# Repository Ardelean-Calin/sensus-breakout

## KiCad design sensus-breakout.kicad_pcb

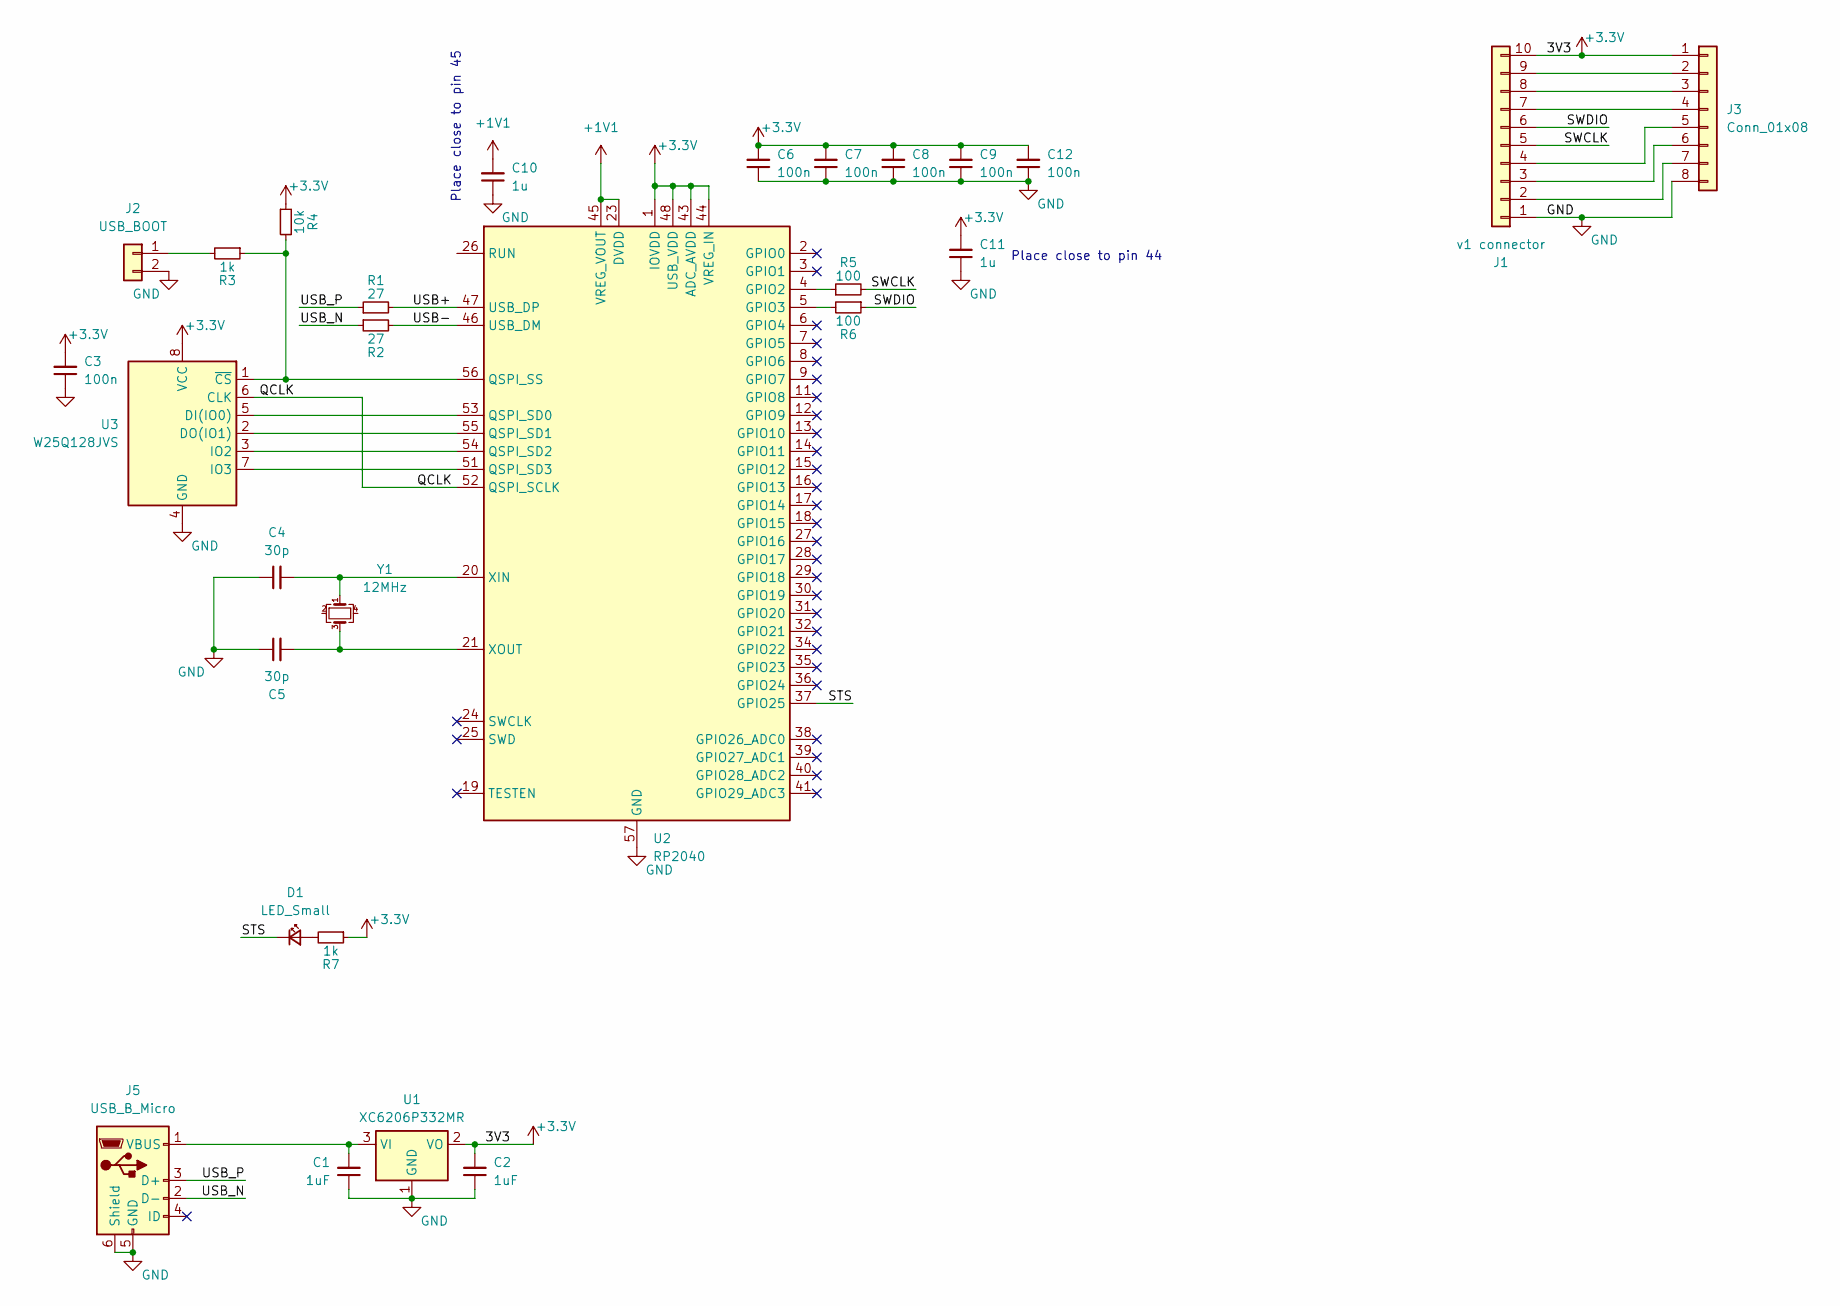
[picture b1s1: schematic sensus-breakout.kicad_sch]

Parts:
C1, C2: 1uF; C_0402_1005Metric; LCSC C52923
C3, C6, C7, C8, C9, C12: 100n; C_0402_1005Metric; LCSC C307331
C4, C5: 30p; C_0402_1005Metric; LCSC C1570
C10, C11: 1u; C_0402_1005Metric; LCSC C52923
D1: LED_Small; LED_0603_1608Metric; LCSC C72043
J1: v1 connector; Hirose_FH12-10S-0.5SH_1x10-1MP_P0.50mm_Horizontal; LCSC C506791
J2: USB_BOOT; PinHeader_1x02_P2.54mm_Vertical
J3: Conn_01x08; PinHeader_1x08_P2.54mm_Vertical
J5: USB_B_Micro; USB_Micro-B_Amphenol_10118193-0001LF_Horizontal; LCSC C132562
R1, R2: 27; R_0603_1608Metric; LCSC C25190
R3, R7: 1k; R_0402_1005Metric; LCSC C11702
R4: 10k; R_0402_1005Metric; LCSC C25744
R5, R6: 100; R_0402_1005Metric; LCSC C25076
U1: XC6206P332MR; SOT-23; LCSC C5446
U2: RP2040; QFN-56-1EP_7x7mm_P0.4mm_EP3.2x3.2mm; LCSC C2040
U3: W25Q128JVS; SOIC-8_5.23x5.23mm_P1.27mm; LCSC C97521
Y1: 12MHz; Crystal_SMD_3225-4Pin_3.2x2.5mm; LCSC C9002

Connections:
+1V1: C10.2, U2.23 (DVDD), U2.45 (VREG_VOUT), U2.50 (DVDD)
+3.3V: C2.2, C3.2, C6.2, C7.2, C8.2, C9.2, C11.2, C12.2, J1.10, J3.1, R4.1, R7.1, U1.2 (VO), U2.1 (IOVDD), U2.10 (IOVDD), U2.22 (IOVDD), U2.33 (IOVDD), U2.42 (IOVDD), U2.43 (ADC_AVDD), U2.44 (VREG_IN), U2.48 (USB_VDD), U2.49 (IOVDD), U3.8 (VCC)
/QCLK: U2.52 (QSPI_SCLK), U3.6 (CLK)
/STS: D1.1 (K), U2.37 (GPIO25)
/SWCLK: J1.5, R5.2
/SWDIO: J1.6, R6.1
/USB+: R1.2, U2.47 (USB_DP)
/USB-: R2.2, U2.46 (USB_DM)
/USB_N: J5.2 (D-), R2.1
/USB_P: J5.3 (D+), R1.1
GND: C1.1, C2.1, C3.1, C4.1, C5.1, C6.1, C7.1, C8.1, C9.1, C10.1, C11.1, C12.1, J1.1, J2.2, J3.8, J5.5 (GND), J5.6 (Shield), U1.1 (GND), U2.57 (GND), U3.4 (GND)
unnamed: D1.2 (A), R7.2
unnamed: J1.2, J3.7
unnamed: J1.3, J3.6
unnamed: J1.4, J3.5
unnamed: J1.7, J3.4
unnamed: J1.8, J3.3
unnamed: J1.9, J3.2
unnamed: J2.1, R3.2
unnamed: C1.2, J5.1 (VBUS), U1.3 (VI)
unnamed: R5.1, U2.4 (GPIO2)
unnamed: R6.2, U2.5 (GPIO3)
unnamed: U2.53 (QSPI_SD0), U3.5 (DI(IO0))
unnamed: U2.55 (QSPI_SD1), U3.2 (DO(IO1))
unnamed: U2.54 (QSPI_SD2), U3.3 (IO2)
unnamed: U2.51 (QSPI_SD3), U3.7 (IO3)
unnamed: R3.1, R4.2, U2.56 (QSPI_SS), U3.1 (~CS)
unnamed: C4.2, U2.20 (XIN), Y1.1
unnamed: C5.2, U2.21 (XOUT), Y1.3

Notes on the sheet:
Place close to pin 44
Place close to pin 45

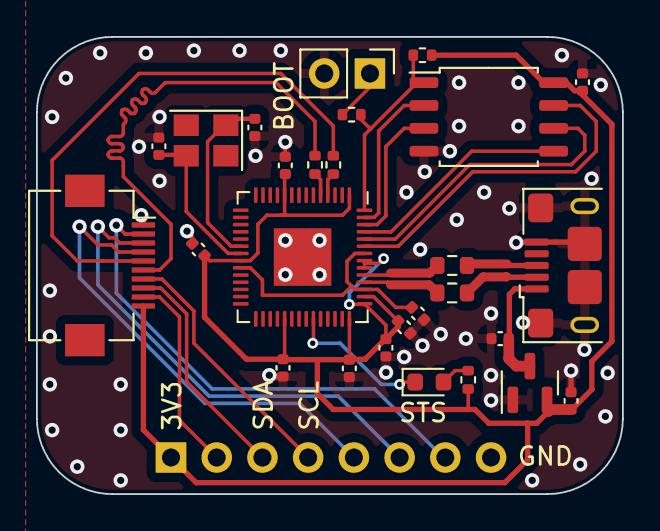
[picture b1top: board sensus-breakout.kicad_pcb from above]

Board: 2 copper layers, 32.6 x 25.4 mm, 28 parts (1 on the bottom side), 29 nets.

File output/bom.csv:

Comment,Designator,Footprint,LCSC
1k,"R3,R7",Resistor_SMD:R_0402_1005Metric,C11702
100,"R5,R6",Resistor_SMD:R_0402_1005Metric,C25076
v1 connector,J1,Connector_FFC-FPC:Hirose_FH12-10S-0.5SH_1x10-1MP_P0.50mm_Horizontal,C506791
Conn_01x08,J3,Connector_PinHeader_2.54mm:PinHeader_1x08_P2.54mm_Vertical,
100n,"C3,C6,C7,C8,C9,C12",Capacitor_SMD:C_0402_1005Metric,C307331
XC6206P332MR,U1,Package_TO_SOT_SMD:SOT-23,C5446
1u,"C10,C11",Capacitor_SMD:C_0402_1005Metric,C52923
1uF,"C1,C2",Capacitor_SMD:C_0402_1005Metric,C52923
30p,"C4,C5",Capacitor_SMD:C_0402_1005Metric,C1570
W25Q128JVS,U3,Package_SO:SOIC-8_5.23x5.23mm_P1.27mm,C97521
10k,R4,Resistor_SMD:R_0402_1005Metric,C25744
USB_BOOT,J2,Connector_PinHeader_2.54mm:PinHeader_1x02_P2.54mm_Vertical,
27,"R1,R2",Resistor_SMD:R_0603_1608Metric,C25190
USB_B_Micro,J5,Connector_USB:USB_Micro-B_Amphenol_10118193-0001LF_Horizontal,C132562
12MHz,Y1,Crystal:Crystal_SMD_3225-4Pin_3.2x2.5mm,C9002
RP2040,U2,Package_DFN_QFN:QFN-56-1EP_7x7mm_P0.4mm_EP3.2x3.2mm,C2040
LED_Small,D1,LED_SMD:LED_0603_1608Metric,C72043

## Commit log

2023-07-20 Initial breakout board revision.
2023-08-20 Ordered second version of breakout board.
